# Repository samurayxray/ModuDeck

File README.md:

# ModuDeck. 3D print exports

Five STL models provided were converted to OBJ and 3MF. The units are assumed to be millimeters (STL files do not have embedded units). All five STL meshes are watertight and have volume. Mechanical fit, print orientation, tolerances and print-bed compatibility are not verified. 01-Assieme and 03-interno-con-PCB are assembly models or reference models, not single-piece prints. 02-Esploso was not provided as an STL file.

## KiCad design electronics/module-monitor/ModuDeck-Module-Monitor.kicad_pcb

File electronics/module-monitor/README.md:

# ModuDeck Module Monitor — routed KiCad design

This folder is the **canonical editable electronics project**. Open [ModuDeck-Module-Monitor.kicad_pro](ModuDeck-Module-Monitor.kicad_pro) in **KiCad 10.0.7 or later**. The completed schematic and routed two-layer PCB are present here. Old KiCad files at the repository root are retained as historical work and must not be used for manufacturing this revision. The main repository's `JOURNAL.md` and `BOM.md` were not modified.

## Completed work and limits

The existing schematic was completed from its first input channel. The initially empty board now contains a 90 x 70mm two-layer layout, three dry-contact inputs, three red LED outputs, two removable Pico socket rows, four M3 holes, screw copper keepouts and ground pours on both faces. All carrier electrical parts are through-hole. The original RP2040 Pico remains a removable assembled module. USB and BOOTSEL are accessible from above.

**ERC: 0 errors, 0 warnings. DRC: 0 violations, 0 unconnected items, 0 schematic-parity issues.** Independent net/pad/geometry/export assertions passed. The existing firmware test and six additional host simulation tests passed. These are software checks. **No fabricated PCB, physical assembly, Pico hardware test, real USB serial test, switch actuation test or enclosure fit test has been performed.** See [CHECKS.md](CHECKS.md) and raw reports in [checks/](checks/).

The outline, mounting pattern and cable/headroom allowances are provisional because the bay has not been measured. See [MECHANICAL.md](MECHANICAL.md). Review physical fit and test a Pico before ordering production. No components or PCBs were ordered.

## Circuit

| Channel | Input GPIO / Pico pin | Pull-up | Series to J pin 1 | LED GPIO / Pico pin | LED resistor |
|---|---|---|---|---|---|
| Tray 1 | GP2 / 4 | R1 10k to 3V3 | R2 1k / J1 | GP10 / 14 | R7 1k / D1 |
| Tray 2 | GP3 / 5 | R3 10k to 3V3 | R4 1k / J2 | GP11 / 15 | R8 1k / D2 |
| Tray 3 | GP4 / 6 | R5 10k to 3V3 | R6 1k / J3 | GP12 / 16 | R9 1k / D3 |

Pico **pin 36 is 3V3 OUT**. All J pin 2 connections and LED cathodes share GND; the carrier connects Pico GND pins 3, 8, 13, 18, 23, 28 and 38. AGND 33 is unused on the carrier and referenced internally by Pico. VBUS 40, VSYS 39, ADC_VREF 35, 3V3_EN 37, RUN 30 and unused GPIOs have intentional no-connect markers. Their socket pads have no carrier traces.

The external normally-open microswitch closes J pin 1 to J pin 2 when seated. GPIO -> 1k -> LED anode; cathode -> GND. D1-D3 pad 1 = K, pad 2 = A. Closed input voltage is nominally **0.30V**, approximately **0.328V** with worst-case 5% resistor tolerances at nominal 3.3V. RP2040 specifies VIL <= 0.8V and VIH >= 2.0V at IOVDD=3.3V. Open input is pulled to 3.3V. LED current is estimated at **1.3mA** for Vf=2.0V; these are calculations, not measurements.

The sole supply/data path is the original Pico micro-USB. No external power input, PC power output, battery connection or charger is added. This PCB observes contacts and does not power trays. A broken switch cable reports absent; presence cannot distinguish removal from cable failure.

## Delivered files

- [Editable schematic](ModuDeck-Module-Monitor.kicad_sch) and [routed PCB](ModuDeck-Module-Monitor.kicad_pcb)
- [Schematic PDF](exports/schematic.pdf)
- [Gerber/Excellon ZIP](exports/ModuDeck-Module-Monitor-manufacturing.zip) and [uncompressed files/drill maps](exports/gerbers/)
- [PCB symbol BOM](exports/pcb-bom.csv) and [expanded purchasing BOM](exports/purchasing-bom.csv), including sockets, headers, external parts, minimum quantities, links and price status
- [Component and price notes](COMPONENTS.md), [mechanical assumptions](MECHANICAL.md), [checks](CHECKS.md)
- [English completed-work description](COMPLETED-WORK.txt)

`fp-lib-table` registers project-local footprints. STEP models in `models/` use `${KIPRJMOD}` paths. Used symbol definitions are cached in the schematic; standard KiCad symbol libraries support library comparisons. The A1 assembly footprint contains both female 1x20 sockets, with original Pico numbering. [THIRD-PARTY.md](THIRD-PARTY.md) records library attribution.

The manufacturing ZIP contains seven Gerbers (F/B copper, F/B mask, F/B silkscreen, Edge.Cuts), a Gerber job file and separate PTH/NPTH drills. It has **70 plated component holes, four 3.2mm non-plated mounting holes and no vias**. No stencil files are needed. File completeness and drill counts were checked; no fabricator CAM acceptance or quote was obtained.

## Firmware and USB serial

Install official MicroPython for **RPI_PICO / original RP2040 Pico**, then copy [firmware/main.py](firmware/main.py) and [firmware/logic.py](firmware/logic.py) to the Pico filesystem root. Existing firmware was retained and updated to disable internal pull-ups explicitly because this board supplies external 10k pull-ups. Inputs are active low with independent 30ms debounce and 5ms polling. GP10/11/12 light for confirmed presence. Startup starts absent until the debounce confirms a closed contact.

RP2 MicroPython stdout uses USB CDC serial, shared with REPL. One newline-terminated JSON message is printed on startup, each confirmed change and once per second while unchanged: `{"type":"modudeck_presence","trays":[true,false,true]}`. Tray order is 1,2,3. Host readers should accept matching JSON and ignore REPL/startup banners. A heartbeat alone does not implement host disconnection handling. Ctrl-C exits the loop and turns off LEDs in `finally`. No UART is configured.

Run `python test_logic.py` and `python test_firmware.py`. Simulations use fake GPIO/time objects to validate the actual main loop; they do not run on RP2040 or transmit through physical USB. Firmware deployment has not been performed on a Pico.

## Six actual design images

These are exported KiCad drawings/renders, **not hardware photos or AI-generated illustrations**. Bottom copper is mirrored for a solder-side view. Old conceptual images in `docs/01-architecture.png` through `docs/04-pcb-placement.png` remain historical planning illustrations.

| Image | Source |
|---|---|
| [Full schematic](exports/images/01-schematic-complete.png) | Completed KiCad schematic PDF |
| [Input detail](exports/images/02-input-detail.png) | PDF crop of all three inputs |
| [LED detail](exports/images/03-led-detail.png) | PDF crop of all three LED paths |
| [PCB top](exports/images/04-pcb-top.png) | F.Cu + F.SilkS + Edge.Cuts |
| [PCB bottom](exports/images/05-pcb-bottom.png) | Mirrored B.Cu + B.SilkS + Edge.Cuts |
| [3D view](exports/images/06-board-3d.png) | KiCad renderer with local STEP models, also `exports/cover.png` |

## Sources

- [Official original Pico pinout](https://datasheets.raspberrypi.com/pico/Pico-R3-A4-Pinout.pdf)
- [Official Pico datasheet](https://datasheets.raspberrypi.com/pico/pico-datasheet.pdf), mechanical/pin allocation and powerchain sections
- [Official RP2040 datasheet](https://datasheets.raspberrypi.com/rp2040/rp2040-datasheet.pdf), section 5.5.3.4, Table 625
- [MicroPython RP2 quick reference](https://docs.micropython.org/en/latest/rp2/quickref.html) and [Pin API](https://docs.micropython.org/en/latest/library/machine.Pin.html)
- Exact parts, drawings and seller links in [COMPONENTS.md](COMPONENTS.md) and the purchasing BOM

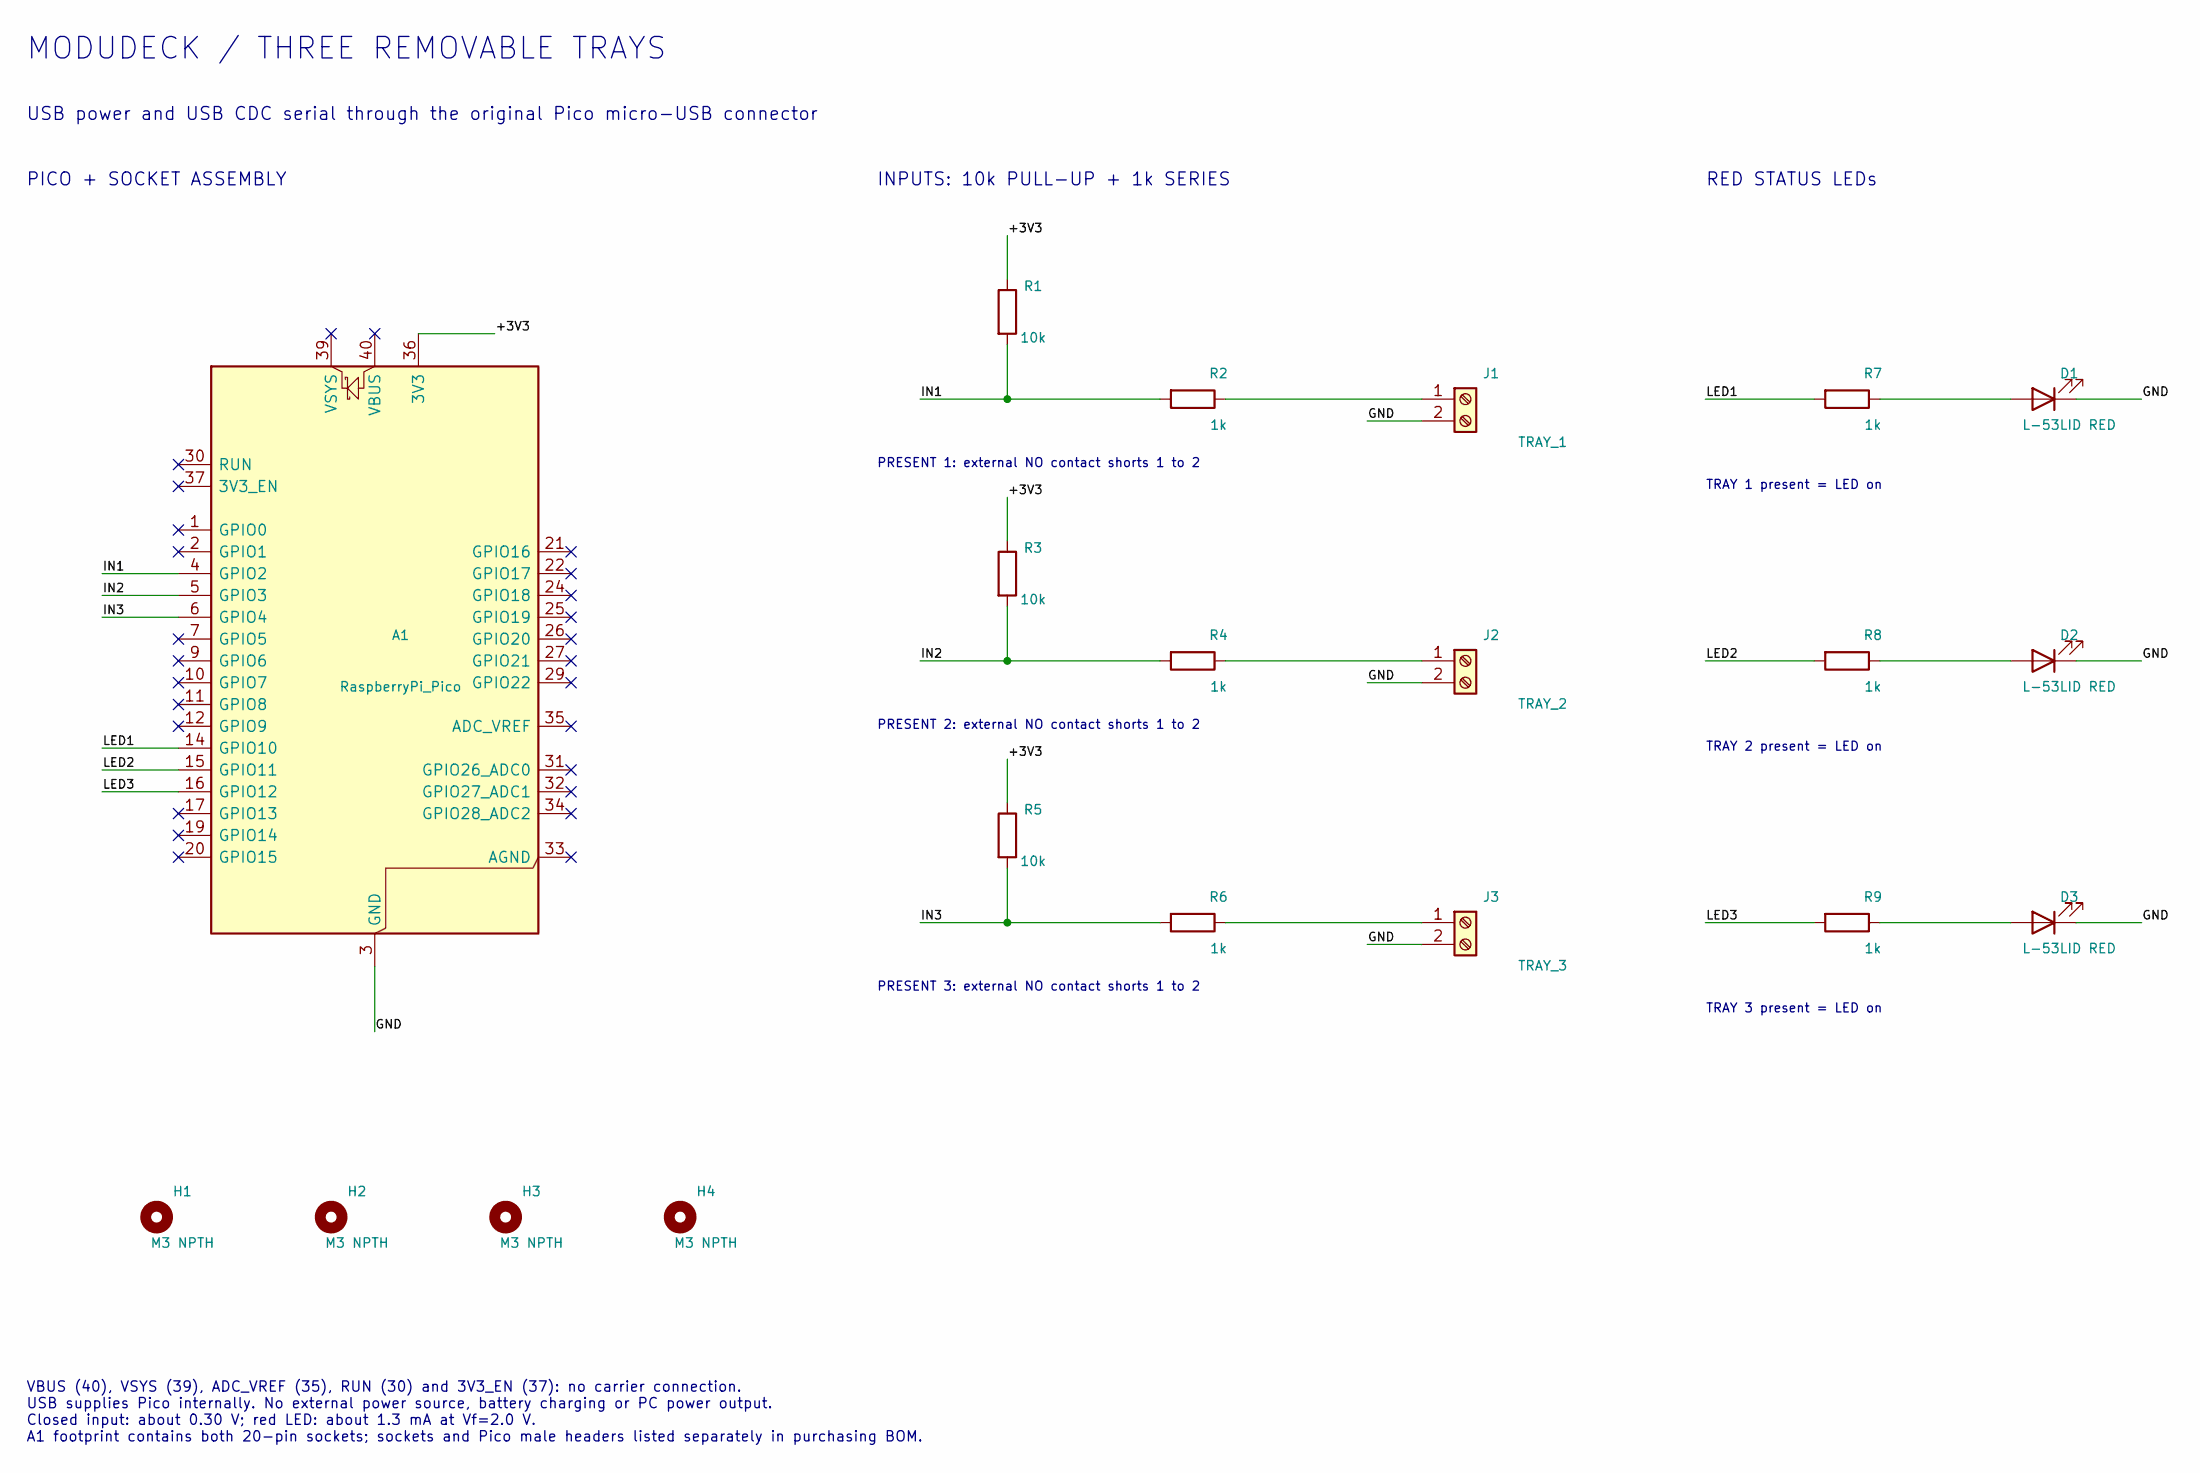
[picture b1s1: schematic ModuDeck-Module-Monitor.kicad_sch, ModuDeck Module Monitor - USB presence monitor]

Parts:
A1: RaspberryPi_Pico; RaspberryPi_Pico_Common_Socketed
D1, D2, D3: L-53LID RED; LED_D5.0mm
H1, H2, H3, H4: M3 NPTH; MountingHole_3.2mm_M3
J1: TRAY_1; TerminalBlock_Phoenix_MKDS-1,5-2-5.08_1x02_P5.08mm_Horizont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
J2: TRAY_2; TerminalBlock_Phoenix_MKDS-1,5-2-5.08_1x02_P5.08mm_Horizont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
J3: TRAY_3; TerminalBlock_Phoenix_MKDS-1,5-2-5.08_1x02_P5.08mm_Horizont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
R1, R3, R5: 10k; R_Axial_DIN0207_L6.3mm_D2.5mm_P10.16mm_Horizontal
R2, R4, R6, R7, R8, R9: 1k; R_Axial_DIN0207_L6.3mm_D2.5mm_P10.16mm_Horizontal

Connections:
/+3V3: A1.36 (3V3), R1.1, R3.1, R5.1
/GND: A1.3 (GND), A1.8 (GND), A1.13 (GND), A1.18 (GND), A1.23 (GND), A1.28 (GND), A1.38 (GND), D1.1 (K), D2.1 (K), D3.1 (K), J1.2, J2.2, J3.2
/IN1: A1.4 (GPIO2), R1.2, R2.2
/IN2: A1.5 (GPIO3), R3.2, R4.2
/IN3: A1.6 (GPIO4), R5.2, R6.2
/LED1: A1.14 (GPIO10), R7.2
/LED2: A1.15 (GPIO11), R8.2
/LED3: A1.16 (GPIO12), R9.2
unnamed: D1.2 (A), R7.1
unnamed: D2.2 (A), R8.1
unnamed: D3.2 (A), R9.1
unnamed: J1.1, R2.1
unnamed: J2.1, R4.1
unnamed: J3.1, R6.1

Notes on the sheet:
PRESENT 1: external NO contact shorts 1 to 2
TRAY 1 present = LED on
PRESENT 2: external NO contact shorts 1 to 2
TRAY 2 present = LED on
PRESENT 3: external NO contact shorts 1 to 2
TRAY 3 present = LED on
MODUDECK / THREE REMOVABLE TRAYS
USB power and USB CDC serial through the original Pico micro-USB connector
PICO + SOCKET ASSEMBLY
INPUTS: 10k PULL-UP + 1k SERIES
RED STATUS LEDs
VBUS (40), VSYS (39), ADC_VREF (35), RUN (30) and 3V3_EN (37): no carrier connection. USB supplies Pico internally. No external power source, battery charging or PC power output. Closed input: about 0.30 V; red LED: about 1.3 mA at Vf=2.0 V. A1 footprint contains both 20-pin sockets; sockets and Pi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

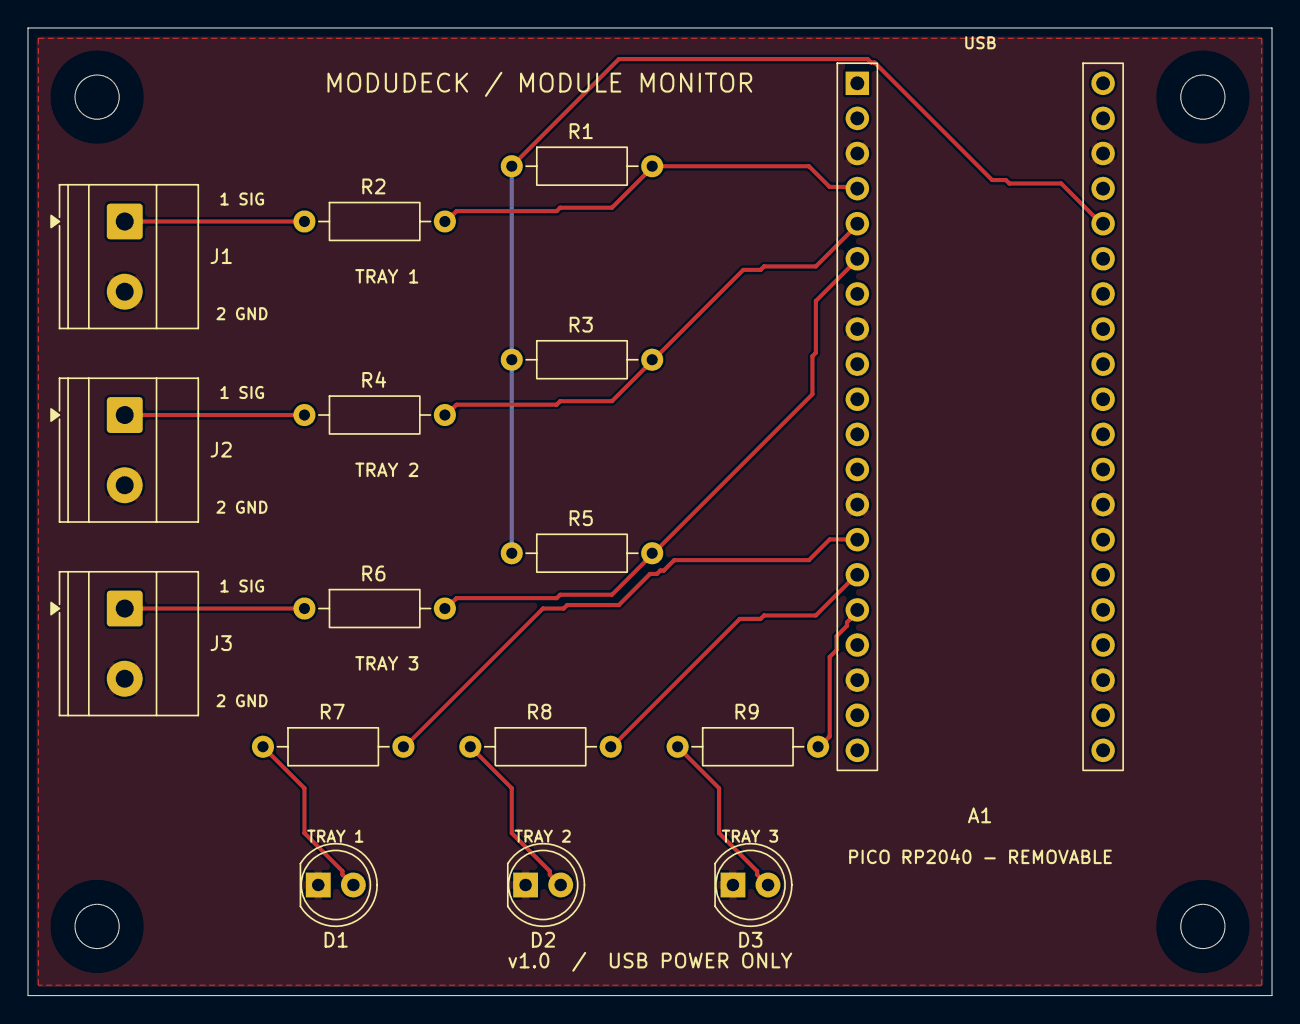
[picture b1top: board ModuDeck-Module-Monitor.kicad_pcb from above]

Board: 2 copper layers, 90.0 x 70.0 mm, 20 parts (0 on the bottom side), 14 nets.

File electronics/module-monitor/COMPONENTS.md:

# Component selection and purchasing BOM

Public vendor listings were checked on **12 October 2026**. Values below are list prices, not a binding checkout quote. No parts were ordered. Shipping for every seller is **da verificare**: no delivery address or cart quote was used. VAT is excluded from EUR prices below. Prices can change.

| Part / references | Needed | Observed purchase quantity | MPN | Seller and observed unit price |
|---|---:|---:|---|---|
| Original Pico / A1 | 1 | 1 | SC0915 | [DigiKey](https://www.digikey.it/it/products/detail/raspberry-pi/SC091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 EUR 4.03 |
| Female sockets, included in A1 footprint | 2 | 2 | CONNFLY DS1023-1*20S21, TME ZL262-20SG | [TME](https://www.tme.eu/it/details/zl262-20sg/connettore-dell-int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 EUR 0.38 |
| Male headers, soldered to Pico | 2 | 10 minimum | CONNFLY DS1021-1*20SF11-B, TME ZL201-20G | [TME international listing](https://www.tme.eu/en/details/zl201-20g/pin-headers/connfly/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 USD 0.20 at 10; EUR price da verificare |
| 10k pull-ups / R1,R3,R5 | 3 | 3 | YAGEO CFR-25JB-52-10K | [DigiKey](https://www.digikey.it/it/products/detail/yageo/CFR-25JB-52-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 EUR 0.09 |
| 1k series / R2,R4,R6,R7,R8,R9 | 6 | 6 | YAGEO CFR-25JB-52-1K | [DigiKey](https://www.digikey.it/it/products/detail/yageo/CFR-25JB-52-1K/96): EUR 0.09 |
| Red LEDs / D1-D3 | 3 | 5 minimum | Kingbright L-53LID | [TME](https://www.tme.eu/it/details/l-53lid/diodi-led-tht-rotondi/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 EUR 0.21 at 5 |
| Screw terminals / J1-J3 | 3 | 3 | Phoenix Contact 1715721 | [DigiKey](https://www.digikey.it/it/products/detail/phoenix-contact/17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 EUR 1.02 |
| External microswitch candidate | 3 | 3 | D2F-01L | [DigiKey](https://www.digikey.it/it/products/detail/aratas-america-llc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 EUR 1.26; final suitability da verificare |

The verified EUR purchasing subtotal for Pico, female sockets, nine resistors, **five purchased LEDs** and three terminals is **EUR 9.71 excluding VAT**. This is a partial subtotal, not the project total. The candidate switches add EUR 3.78. Male headers are separately USD 2.00 for ten; no exchange rate conversion is claimed. USB data cable (candidate StarTech UUSBHAUB1M), wire lengths, PCB fabrication, eight M3 screws and four provisional 5mm insulating standoffs are included in [purchasing-bom.csv](exports/purchasing-bom.csv) with unverified prices left blank and marked **da verificare**.

The two sockets are physically separate parts but are deliberately represented by one A1 assembly footprint: left pad row 1-20 and right pad row 40-21, with 17.78mm spacing and 2.54mm pitch. Sockets are 8.5mm high. Do not solder Pico directly to the carrier. SC0915 is the original RP2040 Pico without headers; add both male strips to it. A pre-headered original Pico H SC0917 is an alternative, not an additional BOM item. It has not been substituted in the purchasing calculation.

Resistor bodies fit the DIN0207 footprint (6.3mm length, 2.5mm nominal diameter, 10.16mm formed lead spacing; 0.8mm holes). The YAGEO body is 6.3 x 2.4mm. LED lead pitch is 2.54mm and hole size 0.9mm: **pad 1 is cathode, pad 2 anode**. Phoenix 1715721 has 5.08mm pitch and recommended 1.3mm holes, matching the footprint. Screw terminals need no mating plug; the two switch wires can be removed by releasing the screws.

The external microswitch is not mounted on this PCB. D2F-01L is a sourcing candidate because tray travel and mounting geometry are not defined. Use only NO and COM, leave NC insulated. Contact reliability/life at the circuit's approximately 0.30mA, 3.3V dry-contact load is **not verified**. The exact switch, lever travel and cable lengths must be selected after measuring the trays and tested on hardware. This does not alter the requested resistor circuit.

Geometry sources: [Pico official datasheet](https://datasheets.raspberrypi.com/pico/pico-datasheet.pdf), [CONNFLY socket drawing](https://www.tme.eu/Document/951e887d7e645db1a4e49e0834499c9b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, [Phoenix official 1715721](https://www.phoenixcontact.com/de-de/produkte/leiterplattenk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, and the linked vendor specification pages. Socket/header seating and LED polarity still require a physical assembly check.
